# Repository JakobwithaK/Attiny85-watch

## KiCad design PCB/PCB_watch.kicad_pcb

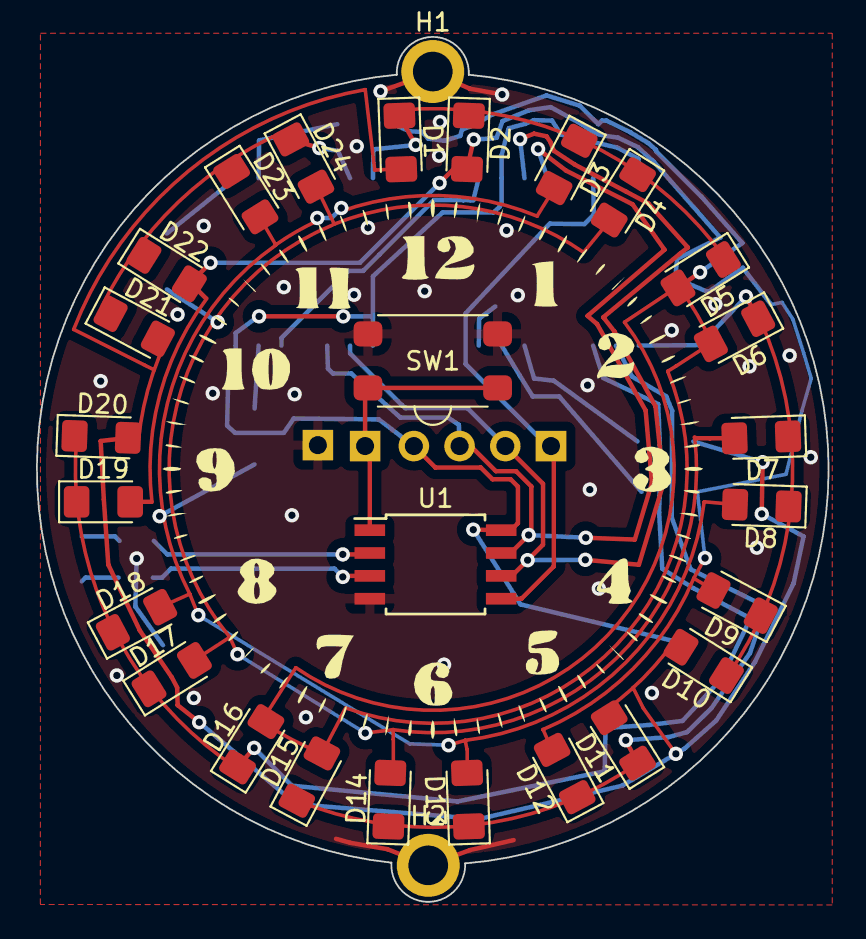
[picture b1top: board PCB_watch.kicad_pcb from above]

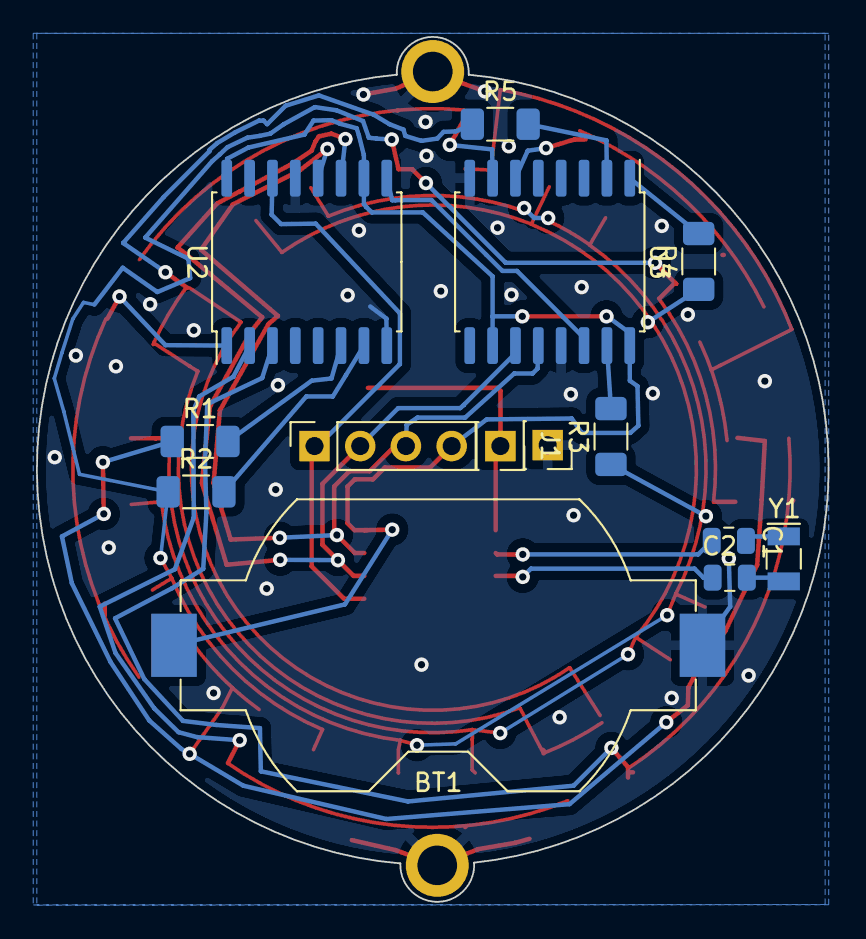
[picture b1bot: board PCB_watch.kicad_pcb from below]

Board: 2 copper layers, 44.0 x 48.1 mm, 42 parts (14 on the bottom side), 26 nets.

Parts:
BT1: Battery_Cell; BatteryHolder_Keystone_1058_1x2032
C1, C2: C; C_0805_2012Metric
D1, D2, D3, D4, D5, D6, D7, D8, D9, D10, D11, D12, D13, D14, D15, D16, D17, D18, D19, D20, D21, D22, D23, D24: LED; D_1206_3216Metric_Pad1.42x1.75mm_HandSolder
H1, H2: MountingHole_Pad; MountingHole_2.2mm_M2_ISO7380_Pad
J1, J2: Conn_01x01_Female; PinSocket_1x01_P2.54mm_Vertical
J3: Conn_01x04_Female; PinSocket_1x04_P2.54mm_Vertical
R1, R2, R3, R4, R5: 100; R_1206_3216Metric_Pad1.30x1.75mm_HandSolder
SW1: SW_Push; TL3305AF160QG_Push_Button
U1: ATtiny85-20S; SOIC-8W_5.3x5.3mm_P1.27mm
U2, U3: 74HC595; SOIC-16W_7.5x10.3mm_P1.27mm
Y1: Crystal; Crystal_SMD_EuroQuartz_EQ161-2Pin_3.2x1.5mm

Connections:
GND: BT1.2 (-), H1.1, H2.1, J2.1, SW1.2, U1.4 (GND), U2.8 (GND), U2.13 (~OE), U3.8 (GND), U3.13 (~OE)
unnamed: C1.1, Y1.1
unnamed: C1.2, U1.2 (XTAL1/PB3)
unnamed: C2.1, U1.3 (XTAL2/PB4)
unnamed: C2.2, Y1.2
unnamed: D1.2 (A), D10.2 (A), D11.2 (A), D20.2 (A), D21.2 (A), R1.1
unnamed: D6.1 (K), D7.1 (K), D8.1 (K), D9.1 (K), D10.1 (K), U2.1 (QB)
unnamed: D11.1 (K), D12.1 (K), D13.1 (K), D14.1 (K), D15.1 (K), U2.2 (QC)
unnamed: D2.2 (A), D9.2 (A), D12.2 (A), D19.2 (A), D22.2 (A), R2.1
unnamed: D3.2 (A), D8.2 (A), D13.2 (A), D18.2 (A), D23.2 (A), R3.1
unnamed: D4.2 (A), D7.2 (A), D14.2 (A), D17.2 (A), D24.2 (A), R4.1
unnamed: D5.2 (A), D6.2 (A), D15.2 (A), D16.2 (A), R5.1
unnamed: D16.1 (K), D17.1 (K), D18.1 (K), D19.1 (K), D20.1 (K), U2.3 (QD)
unnamed: D21.1 (K), D22.1 (K), D23.1 (K), D24.1 (K), U3.6 (QG)
unnamed: J1.1, SW1.1, U1.1 (~RESET/PB5)
unnamed: R1.2, U2.6 (QG)
unnamed: R2.2, U2.7 (QH)
unnamed: R3.2, U3.15 (QA)
unnamed: R4.2, U3.1 (QB)
unnamed: R5.2, U3.2 (QC)
unnamed: J3.1, U1.5 (AREF/PB0), U2.14 (SER)
unnamed: J3.2, U1.6 (PB1), U2.11 (SRCLK), U3.11 (SRCLK)
unnamed: J3.3, U1.7 (PB2), U2.12 (RCLK), U3.12 (RCLK)
unnamed: U2.9 (QH'), U3.14 (SER)
unnamed: D1.1 (K), D2.1 (K), D3.1 (K), D4.1 (K), D5.1 (K), U3.7 (QH)
VCC: BT1.1 (+), J3.4, U1.8 (VCC), U2.10 (~SRCLR), U2.16 (VCC), U3.10 (~SRCLR), U3.16 (VCC)

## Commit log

2023-12-23 adding PCB proof of concept
